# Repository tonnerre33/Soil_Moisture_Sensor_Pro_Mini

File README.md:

# Soil Moisture Sensor Pro Mini

# What is this ?

It's the same project than [this ](https://www.openhardware.io/view/338) but without smd components.

I think it's a good node for the beginers ;)

The CR123A is replaced by 2xAAA batteries.

You can order the pcb here : https://PCBs.io/share/z5YOZ

# Features?
* Send Soil moisture mesure every hours
* Send Battery Level every hours if the value has changed
* Send Battery voltage every hours if the percentage has changed

# Compatibilies ?
* Mysensors Library 2.0.0
* PCBs v1.1.x compatibles with SoilMoisture_Sensor_Pro_Mini_v1.1.x Sketchs

# Logs PCB :

## V1.1
* 21/02/2017 = Fabrication V1.1 by PCBs.io => Awaiting Panelization
* 27/02/2017 = Fabrication V1.1 by PCBs.io => In Fabrication
* 08/03/2017 = Fabrication V1.1 by PCBs.io => Shipped
* 15/03/2017 = Fabrication V1.1 by PCBs.io => Received
* 15/03/2017 = Assembly and Test => OK

# Logs Sketch:
## V1.1.2
* Add default values
* Do not send moisture to the controler if she didn't change more than 1%
* Change Low Fuse example

## V1.1.3 - In progress
* Fixed "Do not send moisture to the controler if she didn't change more than 1%"
* Added possibility to blink the "info" led when insufficient moisture
* Added possibility to blink the "warning" led when insufficient battery
* Added possibility to use this node without controler (need mysensors >= 2.1.0)
* Disable smartsleep when not OTA used (increase battery life)

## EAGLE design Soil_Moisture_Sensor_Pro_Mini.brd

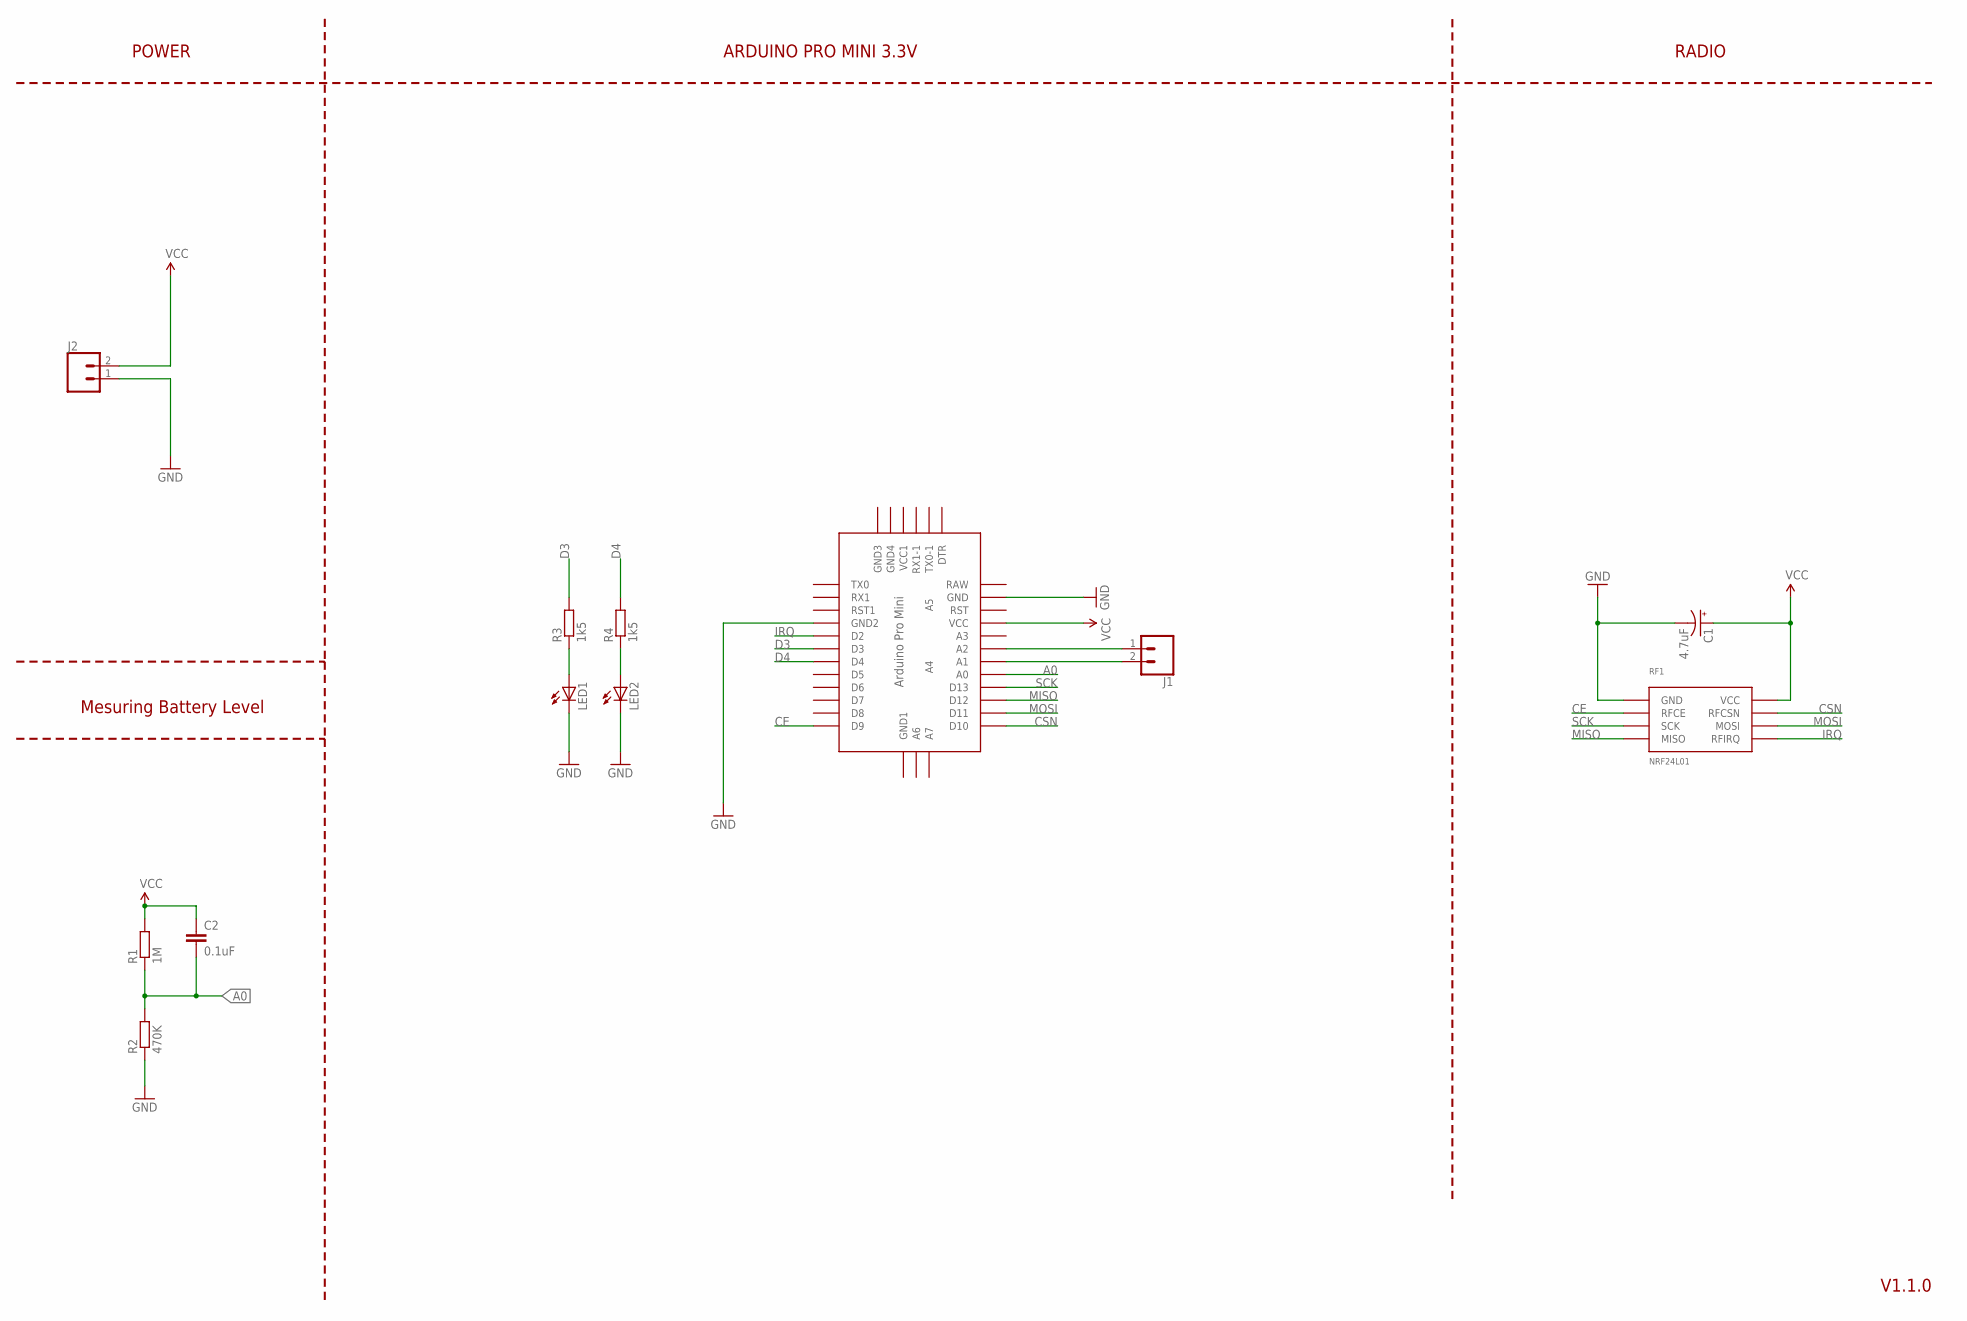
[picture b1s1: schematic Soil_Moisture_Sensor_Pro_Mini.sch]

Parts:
C1: 4.7uF; E2,5-6E
C2: 0.1uF; C025-025X050
J1, J2: CONN_02; 1X02
LED1, LED2: LED3MM
R1: 1M; 0204/7
R2: 470K; 0204/7
R3, R4: 1k5; 0204/7
RF1: NRF24L01; 2X4-2.54MM
U$1: ABK-PRO-MINI

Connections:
A0: C2.2, R1.1, R2.2, U$1.A0
CE: RF1.P$3 (RFCE), U$1.D9
CSN: RF1.P$4 (RFCSN), U$1.D10
D3: R3.2, U$1.D3
D4: R4.2, U$1.D4
GND: C1.-, J2.1, LED1.K (C), LED2.K (C), R2.1, RF1.P$1 (GND), U$1.GND, U$1.GND1 (GND2)
IRQ: RF1.P$8 (RFIRQ), U$1.D2
MISO: RF1.P$7 (MISO), U$1.D12
MOSI: RF1.P$6 (MOSI), U$1.D11
unnamed: J1.1, U$1.A2
unnamed: J1.2, U$1.A1
unnamed: LED2.A, R4.1
unnamed: LED1.A, R3.1
SCK: RF1.P$5 (SCK), U$1.D13
VCC: C1.+, C2.1, J2.2, R1.2, RF1.P$2 (VCC), U$1.VCC

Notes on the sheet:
POWER
ARDUINO PRO MINI 3.3V
RADIO
Mesuring Battery Level
V1.1.0

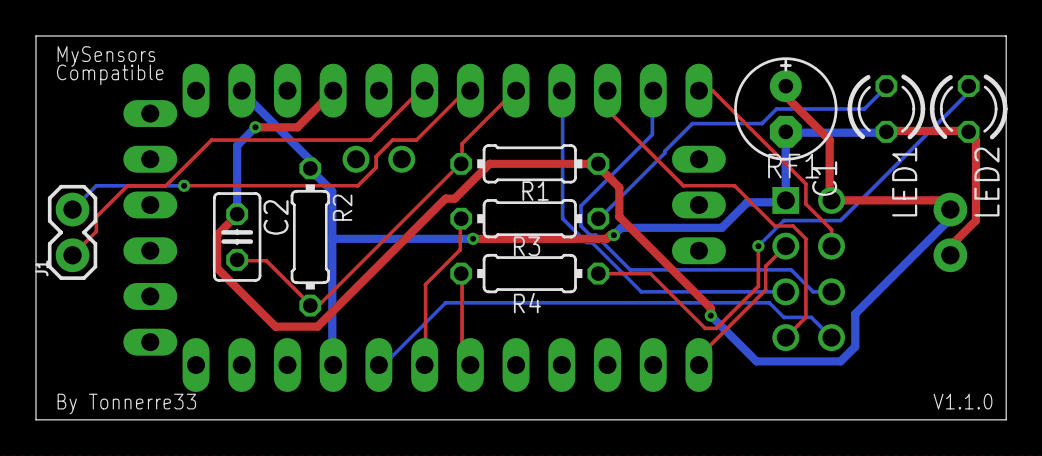
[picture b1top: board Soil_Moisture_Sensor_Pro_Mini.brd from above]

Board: 2 copper layers, 53.9 x 21.3 mm, 12 parts (1 on the bottom side), 15 nets.

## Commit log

2017-03-18 pcb-v1.1
2017-03-18 fw-v1.1.2
2017-03-18 Modify version + Adding standalone mode + Fix soil humidity update value
2017-03-19 fw-1.1.3 Readme
2017-03-19 fw-1.1.3 Move LED PIN info in presentation for compatibility with mysensors >2.1.0
2017-04-13 Comment MY_DEBUG
2017-09-23 fixed mode without gateway & auto indent

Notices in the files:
parts and their libraries:
SparkFun-Connectors: Licensing: Creative Commons ShareAlike 4.0 International - https://creativecommons.org/licenses/by-sa/4.0
